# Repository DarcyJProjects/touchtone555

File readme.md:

# TouchTone555 – NE555 Analogue Stylus Synth

The **TouchTone555** is a fully analogue, NE555-based synthesizer designed for learning about analogue electronics, and a bit of fun too. It was built from scratch as a personal deep-dive into oscillators, signal integrity, analogue filtering, and amplification.

Read the full project write up at: [www.darcyjprojects.xyz](https://www.darcyjprojects.xyz/index.php/2025/04/07/analogue-synth-project-touchtone555/)

[🔗 Share this project on LinkedIn](https://www.linkedin.com/shareArticle?mini=true&url=https://www.darcyjprojects.xyz/index.php/2025/04/07/analogue-synth-project-touchtone555/&title=TouchTone555%20Stylus%20Synth&summary=Check%20out%20this%20analogue%20NE555-based%20synthesizer%20project!)

<p>
  This project is open source hardware under the <strong>CERN Open Hardware Licence Version 2 - Strongly Reciprocal (CERN-OHL-S v2)</strong>.
</p>

⚖️**Disclaimer:** This synthesizer was developed as a purely educational project to explore analogue electronics and sound synthesis. It is an independent work inspired by the vintage Stylophone, with no affiliation to Dubreq Ltd. or the original Stylophone product. All trademarks remain the property of their respective owners, and no copyright or trademark infringement is intended.

---

## 📑 Table of Contents

* 🎛 [Features](#-features)

* 📷 [Demo](#-demo)

* 📜 [Licence](#-licence)

* ⚡[How It Works](#how-it-works)

* 🛠️ [Build Instructions](#%EF%B8%8F-build-instructions)
  
  * 🧾 [What You’ll Need](#-what-youll-need)
  
  * 🪛 [Assembly](#-assembly)

* 📂 [Repo Structure](#-repo-structure)

* 💬 [Feedback & Contributions](#-feedback--contributions)

* 🔗 [Acknowledgements](#-acknowledgements)

* 🧠 [Why I Built This](#-why-i-built-this)

---

## 🎛 Features

- Based on the NE555 in astable multivibrator configuration as the main audio oscillator
- Individually tuneable keys with trim potentiometers
- Touch interface for the keys with a stylus
- Octave switching via capacitor bank selection
- Vibrato modulation using an RC oscillator on the 555's CV pin
- Push-pull amplifier output with an LM386 buffer stage
- Onboard speaker with volume control, as well as a headphone output
- Custom designed PCB, with a descriptive silkscreen

---

## 📷 Demo

Check out the demo video here:<br>
👉 [Watch the video](https://www.youtube.com/watch?v=lvPiY5EYj-0)<br>
<br>
🎵 Features a cover of Littleroot Town from Pokémon.

---

## 📜 Licence

This project is licenced under the **CERN-OHL-S v2 Strongly Reciprocal**.  

You are free to:

- **Study** and **modify** the design.

- **Make** and **sell** your own copies.

- **Distribute** modified versions — **as long as you:**
  
  - **Use the same CERN-OHL-S v2 licence** (strong reciprocity), and
  
  - **Provide attribution to the original author**, and
  
  - **Include the original source files and any modifications**.

For full details, see the [LICENCE.txt](https://github.com/DarcyJProjects/touchtone555/blob/main/LICENCE.txt) file.

---

## ⚡How It Works

The TouchTone555 generates sound using an NE555 timer IC which is configured as an astable multivibrator. 

Each key forms part of a series resistor network, which controls the oscillator’s frequency when the circuit is completed by touching a key with the stylus. The pitch is determined by which key is touched, and the selected octave capacitor.

Octave switching is achieved by toggling between banks of capacitors connected to the NE555. The more capacitance connected (capacitors in parallel), the lower the resulting octave.

Vibrato is achieved by modulating the NE555's control voltage pin using a separate RC oscillator, which uses RC (resistor-capacitor) pairs, capacitors, and a transistor to generate the low-frequency signal. The vibrato depth (or "mix") can be adjusted with the on-board trim potentiometer.

The output signal is then passed through an LM386 and then through a simple push-pull amplifier to drive the onboard speaker and/or headphones. The LM386 acts as a buffer to ensure any loading from the amplifier doesn't affect the NE555 through its output pin. The supply voltage to the NE555 is also filtered with a resistor and capacitor to reduce any periodic voltage drop introduced by the amplifier.

The power supply circuitry is simple: it supports a 9V DC input via either a JST connector, or a DC barrel jack. Two diodes prevent reverse polarity and ensure that the inputs cannot backfeed each other. 

This project demonstrates the core concepts of oscillation, modulation, and amplification - no microcontroller required!

👉 For a full breakdown and more detail explanations, you can read the write-up here: [www.darcyjprojects.xyz](https://www.darcyjprojects.xyz/index.php/2025/04/07/analogue-synth-project-touchtone555/)

---

## 🛠️ Build Instructions

### 🧾 What You’ll Need

- All components as outlined in the [BOM (Bill-of-Materials)](https://github.com/DarcyJProjects/touchtone555/blob/main/hardware/bom.md)
- To find the correct switches, speaker, audio jack, etc, see [Miscellaneous Parts](https://github.com/DarcyJProjects/touchtone555/blob/main/hardware/misc_parts.md)
- PCB (See [KiCad Project](https://github.com/DarcyJProjects/touchtone555/tree/main/hardware))
- Soldering iron and solder
- 9V Battery and connector or DC jack with 9V supply

⚠️ **Note:** I recommend selecting a **lead-free surface finish** (e.g., LeadFree HASL) when ordering the PCB as the stylus will put microscopic scratches in the exposed key pads during use. This could potentially produce harmful lead dust over time. Therefore, I highly recommend choosing lead-free!

### 🪛 Assembly

- Read each step fully before completing it to make sure you've read any handy tips :)
1. **Order the PCB**<br>
   The KiCad project files (and pre-exported gerber files) are located in [/hardware](https://github.com/DarcyJProjects/touchtone555/tree/main/hardware).

2. **Solder components in order**<br>
   Start with the smallest passive components (resistors, monolithic capacitors, diodes), then IC sockets, transistors, connectors/jacks/switches, ceramic and polyester capacitors, and finally the DC jack, trim potentiometers and the volume potentiometer.
   
   Soldering them systematically from smallest height to largest makes it a lot easier! Follow the component designators on the board, and in the BOM to make sure you are matching the correct values and components.
   
   Try your best not to get any solder on the exposed key pads, if you're nervous, you  can tape over them with some electrical or painters tape until you're finished soldering.
   
   For the polyester octave capacitors, try to get the values matched to each other as closely as possible as a small variance of 0.5 nF can throw off the pitch. This is less important for the lower octaves, but the highest octave with the single capacitor matters the most.
   
   For the vibrato monolithic capacitors, you can start with soldering the top three in, and adding the lower two if you want increase the vibrato frequency.

3. **Attach speaker & power**<br>
   The synth is designed to run on 9VDC, so I recommend using a 9V battery with a 9V battery to JST connector.

4. **Stylus**<br>
   
   In [/hardware](https://github.com/DarcyJProjects/touchtone555/tree/main/hardware), there is a 3D model of a stylus if you'd like to 3D print one, otherwise, a crocodile lead works really well too - just be careful not to push down too aggressively as to not damage the key pads.
   
   If you take the 3D model route, you can feed a thin gauge wire through the hole in the centre of the stylus, and solder a small piece of metal to the wire at the tip of the stylus. I used a mini spade connector which I soldered and then bent around the tip. I smoothed out the contact surface by creating a sphere of solder. You'll need to tape the tip to the stylus to ensure it doesn't come off. This stylus isn't perfect, but it works :)

5. **Tune keys**<br>
   Use a tuner app (with a chromatic mode) or oscilloscope to set the individual key pitches via the blue trim potentiometers.
   
   Set the octave to the lowest octave (lowest position on the octave switch) and then start tuning with the highest note on the keyboard, which corresponds to the right-most trim pot. Turning it clockwise will increase the pitch, and anticlockwise will decrease the pitch. You are aiming for the highest note (in the lowest octave) to be E6.
   
   Then work your way leftwards, one potentiometer at a time, reducing the pitch by one semitone each time.
   
   Remember, as this is a series resistor network, adjusting the pitch of one potentiometer will adjust the pitch of all the other keys to the left of that key. This is why you should work right to left.

6. **Vibrato depth**<br>
   By turning the vibrato depth trim pot, you can slightly adjust how strong the vibrato effect is. The change with each turn is minimal, so you'll need to turn it a lot to get any real difference. 

7. **Have fun!**

---

## 📂 Repo Structure

TouchTone555/<br>├── hardware/ # KiCad project + Gerbers + Stylus 3D model<br>├── media/ # Photos, demo videos, renders, etc<br>├── LICENCE # CERN-OHL-S v2<br>└── README.md # this file!<br>

---

### 💬 Feedback & Contributions

Feel free to fork, share, and build your own!<br>
If you build one, I’d love to see it - tag me on [LinkedIn](https://www.linkedin.com/in/darcywdjohnson/).

---

### 🔗 Acknowledgements

- This is an independent work inspired by the classic Stylophone with no affiliation to Dubreq Ltd. or the original Stylophone product. All trademarks remain the property of their respective owners, and no copyright or trademark infringement is intended.
- "Littleroot Town", composed by Gō Ichinose, Junichi Masuda, & Morikazu Aoki, from *Pokémon Ruby, Sapphire, & Emerald* (© Nintendo / Game Freak), is used under fair use as part of an educational demonstration.

---

## 🧠 Why I Built This

This was a personal challenge to push my understanding of analogue electronics beyond textbooks — especially in:

- Oscillator design
- Filtering
- Operational amplifiers
- Audio amplifiers
- Impedance buffering
- PCB design with custom exposed planes (the key pads)
- PCB footprint design

---

🛠️ Built for learning.<br>
❤️ Shared with the community.<br>
🔧 Darcy — [www.darcyjprojects.xyz](https://www.darcyjprojects.xyz)

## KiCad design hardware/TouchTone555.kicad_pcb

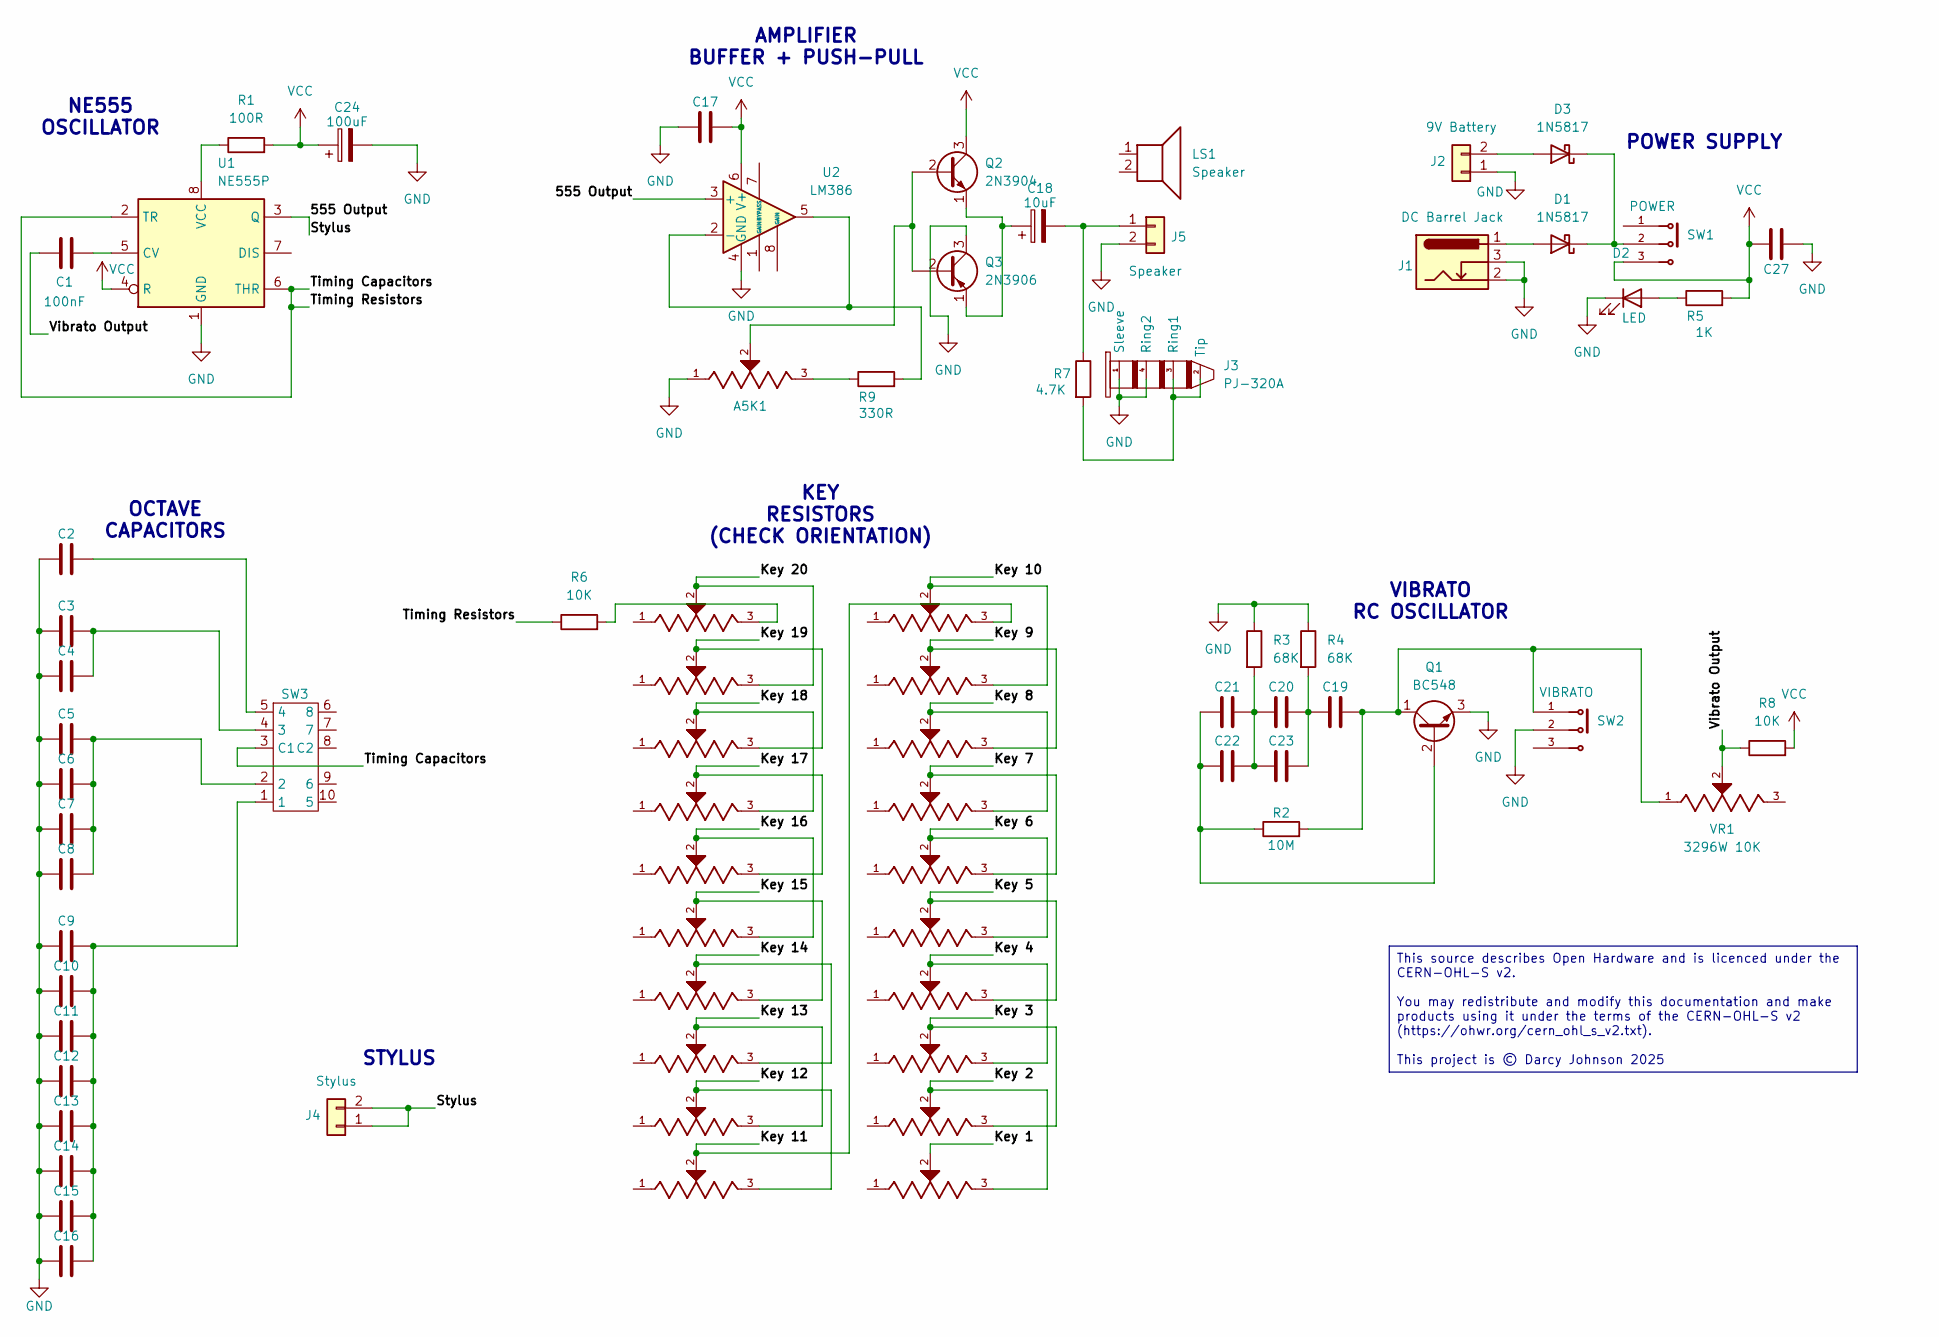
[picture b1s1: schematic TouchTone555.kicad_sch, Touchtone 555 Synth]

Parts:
A5K1: A5K RK097; RV09 Vertical Aliexpress; PARTREV 05/16
C1, C17, C19, C20, C21, C22, C23, C27: 100nF; C_Disc_D5.0mm_W2.5mm_P5.00mm
C2, C3, C4, C5, C6, C7, C8, C9, C10, C11, C12, C13, C14, C15, C16: 10nF; C_Rect_L7.0mm_W2.0mm_P5.00mm
C18: 10uF; CP_Radial_D5.0mm_P2.50mm
C24: 100uF; CP_Radial_D5.0mm_P2.50mm
D1, D3: 1N5817; D_DO-41_SOD81_P10.16mm_Horizontal
D2: LED; LED_D3.0mm
J1: DC Barrel Jack; BarrelJack_CUI_PJ-102AH_Horizontal_BIGGER_HOLES
J2: 9V Battery; JST_PH_B2B-PH-K_1x02_P2.00mm_Vertical
J3: PJ-320A
J4: Stylus; JST_PH_B2B-PH-K_1x02_P2.00mm_Vertical
J5: Speaker; JST_PH_B2B-PH-K_1x02_P2.00mm_Vertical
LS1: Speaker; 8Ω Speaker 40mm
Q1: BC548; TO-92_Inline
Q2: 2N3904; TO-92_Inline
Q3: 2N3906; TO-92_Inline
R1: 100R; R_Axial_DIN0207_L6.3mm_D2.5mm_P7.62mm_Horizontal
R2: 10M; R_Axial_DIN0207_L6.3mm_D2.5mm_P7.62mm_Horizontal
R3, R4: 68K; R_Axial_DIN0207_L6.3mm_D2.5mm_P7.62mm_Horizontal
R5: 1K; R_Axial_DIN0207_L6.3mm_D2.5mm_P7.62mm_Horizontal
R6, R8: 10K; R_Axial_DIN0207_L6.3mm_D2.5mm_P7.62mm_Horizontal
R7: 4.7K; R_Axial_DIN0207_L6.3mm_D2.5mm_P7.62mm_Horizontal
R9: 330R; R_Axial_DIN0207_L6.3mm_D2.5mm_P7.62mm_Horizontal
SW1: POWER; SW_1825159-1; MPN 1825159-1
SW2: VIBRATO; SW_1825159-1; MPN 1825159-1
SW3: SS-24E04_2P4T_Slide_Switch
U1: NE555P; DIP-8_W7.62mm
U2: LM386; DIP-8_W7.62mm
VR1: 3296W 10K; Potentiometer_Bourns_3296W_Vertical; PARTREV 05/16
VR2, VR3, VR4, VR5, VR6, VR7, VR8, VR9, VR10, VR11, VR13, VR14, VR15, VR16, VR17, VR18, VR19, VR20, VR21, VR22: 3296W 5K; Potentiometer_Bourns_3296W_Vertical; PARTREV 05/16

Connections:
/555 Output: J4.1, J4.2, U1.3 (Q), U2.3 (+)
/Key 1: VR22.2
/Key 2: VR21.2, VR22.3
/Key 3: VR20.2, VR21.3
/Key 4: VR19.2, VR20.3
/Key 5: VR18.2, VR19.3
/Key 6: VR17.2, VR18.3
/Key 7: VR16.2, VR17.3
/Key 8: VR15.2, VR16.3
/Key 9: VR14.2, VR15.3
/Key 10: VR13.2, VR14.3
/Key 11: VR11.2, VR13.3
/Key 12: VR10.2, VR11.3
/Key 13: VR9.2, VR10.3
/Key 14: VR8.2, VR9.3
/Key 15: VR7.2, VR8.3
/Key 16: VR6.2, VR7.3
/Key 17: VR5.2, VR6.3
/Key 18: VR4.2, VR5.3
/Key 19: VR3.2, VR4.3
/Key 20: VR2.2, VR3.3
/Timing Capacitors: R6.1, SW3.3 (C1), U1.2 (TR), U1.6 (THR)
/Vibrato Output: C1.2, R8.1, VR1.2
GND: A5K1.1, C2.1, C3.1, C4.1, C5.1, C6.1, C7.1, C8.1, C9.1, C10.1, C11.1, C12.1, C13.1, C14.1, C15.1, C16.1, C17.1, C24.2, C27.1, D2.1 (K), J1.2, J1.3, J2.1, J3.1 (Sleeve), J3.4 (Ring2), J5.2, Q1.3 (E), Q3.3 (C), R3.1, R4.1, SW2.2, U1.1 (GND), U2.4 (GND)
unnamed: A5K1.3, R9.1
unnamed: C5.2, C6.2, C7.2, C8.2, SW3.2
unnamed: C9.2, C10.2, C11.2, C12.2, C13.2, C14.2, C15.2, C16.2, SW3.1
unnamed: C19.1, C20.2, C23.2, R4.2
unnamed: C20.1, C21.2, C22.2, C23.1, R3.2
unnamed: D1.2 (A), J1.1
unnamed: D1.1 (K), D3.1 (K), SW1.2
unnamed: D2.2 (A), R5.1
unnamed: D3.2 (A), J2.2
unnamed: J3.2 (Tip), J3.3 (Ring1), R7.2
unnamed: C18.2, J5.1, R7.1
unnamed: C21.1, C22.1, Q1.2 (B), R2.1
unnamed: C19.2, Q1.1 (C), R2.2, SW2.1, VR1.1
unnamed: A5K1.2, Q2.2 (B), Q3.2 (B)
unnamed: C18.1, Q2.1 (E), Q3.1 (E)
unnamed: R6.2, VR2.3
unnamed: C3.2, C4.2, SW3.4 (3)
unnamed: C2.2, SW3.5 (4)
unnamed: C1.1, U1.5 (CV)
unnamed: R1.1, U1.8 (VCC)
unnamed: R9.2, U2.2 (-), U2.5
VCC: C17.2, C24.1, C27.2, Q2.3 (C), R1.2, R5.2, R8.2, SW1.3, U1.4 (R), U2.6 (V+)

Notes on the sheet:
NE555 OSCILLATOR
STYLUS
VIBRATO RC OSCILLATOR
KEY RESISTORS (CHECK ORIENTATION)
OCTAVE CAPACITORS
AMPLIFIER BUFFER + PUSH-PULL
POWER SUPPLY
This source describes Open Hardware and is licenced under the CERN-OHL-S v2. You may redistribute and modify this documentation and make products using it under the terms of the CERN-OHL-S v2 (https://ohwr.org/cern_ohl_s_v2.txt). This project is © Darcy Johnson 2025

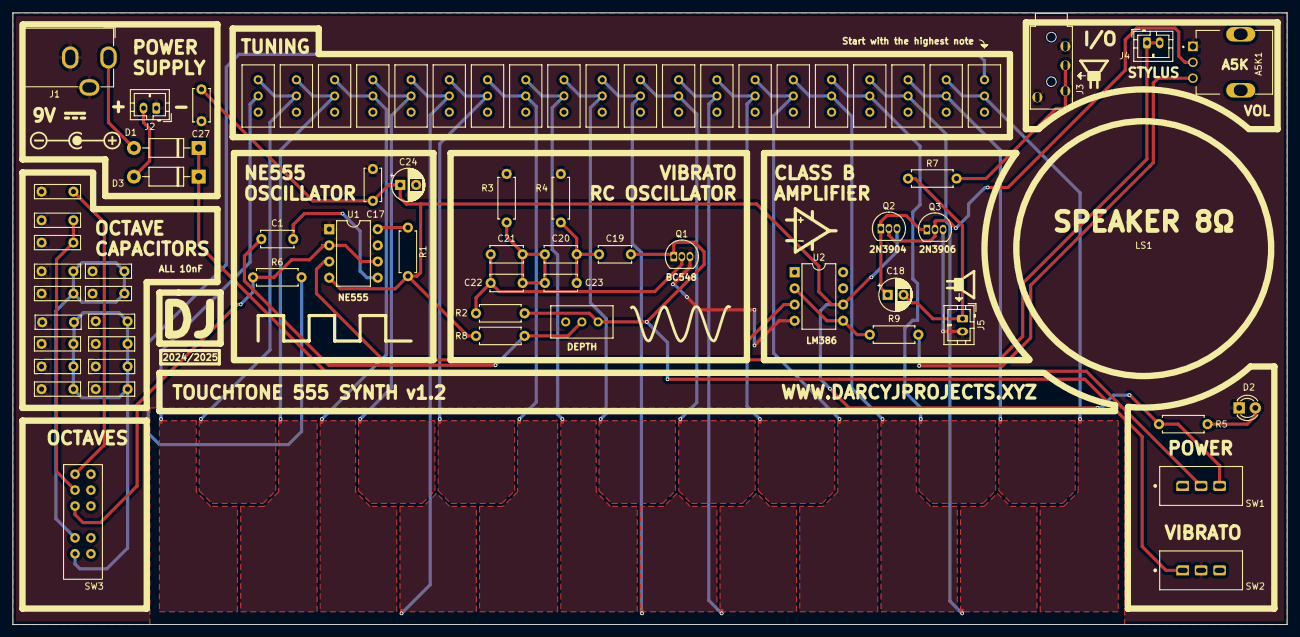
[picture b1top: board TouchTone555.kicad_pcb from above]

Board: 2 copper layers, 200.0 x 96.0 mm, 73 parts (0 on the bottom side), 45 nets.

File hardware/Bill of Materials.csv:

"Id;""Designator"";""Footprint"";""Quantity"";""Designation"";""Supplier and ref"";",,,,,,,,,,,,,,,,,,,
"1;""D1","D3"";""D_DO-41_SOD81_P10.16mm_Horizontal"";2;""1N5817"";;;",,,,,,,,,,,,,,,,,,
"2;""SW3"";""SS-24E04_2P4T_Slide_Switch"";1;""~"";;;",,,,,,,,,,,,,,,,,,,
"3;""R7"";""R_Axial_DIN0207_L6.3mm_D2.5mm_P7.62mm_Horizontal"";1;""4.7K"";;;",,,,,,,,,,,,,,,,,,,
"4;""R1"";""R_Axial_DIN0207_L6.3mm_D2.5mm_P7.62mm_Horizontal"";1;""100R"";;;",,,,,,,,,,,,,,,,,,,
"5;""C18"";""CP_Radial_D5.0mm_P2.50mm"";1;""10uF"";;;",,,,,,,,,,,,,,,,,,,
"6;""SW2"";""SW_1825159-1"";1;""VIBRATO"";;;",,,,,,,,,,,,,,,,,,,
"7;""J4"";""JST_PH_B2B-PH-K_1x02_P2.00mm_Vertical"";1;""Stylus"";;;",,,,,,,,,,,,,,,,,,,
"8;""VR15",VR4,VR5,VR8,VR22,VR11,VR20,VR14,VR9,VR17,VR3,VR6,VR10,VR2,VR13,VR18,VR19,VR7,VR21,"VR16"";""Potentiometer_Bourns_3296W_Vertical"";20;""3296W 5K"";;;"
"9;""C6",C16,C7,C11,C5,C9,C15,C2,C13,C3,C12,C14,C8,C4,"C10"";""C_Rect_L7.0mm_W2.0mm_P5.00mm"";15;""10nF"";;;",,,,,
"10;""Q3"";""TO-92_Inline"";1;""2N3906"";;;",,,,,,,,,,,,,,,,,,,
"11;""C21",C19,C27,C17,C20,C1,C23,"C22"";""C_Disc_D5.0mm_W2.5mm_P5.00mm"";8;""100nF"";;;",,,,,,,,,,,,
"12;""R2"";""R_Axial_DIN0207_L6.3mm_D2.5mm_P7.62mm_Horizontal"";1;""10M"";;;",,,,,,,,,,,,,,,,,,,
"13;""R6","R8"";""R_Axial_DIN0207_L6.3mm_D2.5mm_P7.62mm_Horizontal"";2;""10K"";;;",,,,,,,,,,,,,,,,,,
"14;""R5"";""R_Axial_DIN0207_L6.3mm_D2.5mm_P7.62mm_Horizontal"";1;""1K"";;;",,,,,,,,,,,,,,,,,,,
"15;""R9"";""R_Axial_DIN0207_L6.3mm_D2.5mm_P7.62mm_Horizontal"";1;""330R"";;;",,,,,,,,,,,,,,,,,,,
"16;""U2"";""DIP-8_W7.62mm"";1;""LM386"";;;",,,,,,,,,,,,,,,,,,,
"17;""Q1"";""TO-92_Inline"";1;""BC548"";;;",,,,,,,,,,,,,,,,,,,
"18;""J1"";""BarrelJack_CUI_PJ-102AH_Horizontal_BIGGER_HOLES"";1;""DC Barrel Jack"";;;",,,,,,,,,,,,,,,,,,,
"19;""Q2"";""TO-92_Inline"";1;""2N3904"";;;",,,,,,,,,,,,,,,,,,,
"20;""R4","R3"";""R_Axial_DIN0207_L6.3mm_D2.5mm_P7.62mm_Horizontal"";2;""68K"";;;",,,,,,,,,,,,,,,,,,
"21;""U1"";""DIP-8_W7.62mm"";1;""NE555P"";;;",,,,,,,,,,,,,,,,,,,
"22;""J5"";""JST_PH_B2B-PH-K_1x02_P2.00mm_Vertical"";1;""Speaker"";;;",,,,,,,,,,,,,,,,,,,
"23;""C24"";""CP_Radial_D5.0mm_P2.50mm"";1;""100uF"";;;",,,,,,,,,,,,,,,,,,,
"24;""J2"";""JST_PH_B2B-PH-K_1x02_P2.00mm_Vertical"";1;""9V Battery"";;;",,,,,,,,,,,,,,,,,,,
"25;""A5K1"";""RV09 Vertical Aliexpress"";1;""A5K RK097"";;;",,,,,,,,,,,,,,,,,,,
"26;""LS1"";""8Ω Speaker 40mm"";1;""Speaker"";;;",,,,,,,,,,,,,,,,,,,
"27;""VR1"";""Potentiometer_Bourns_3296W_Vertical"";1;""3296W 10K"";;;",,,,,,,,,,,,,,,,,,,
"28;""SW1"";""SW_1825159-1"";1;""POWER"";;;",,,,,,,,,,,,,,,,,,,
"29;""J3"";""PJ-320A"";1;""PJ-320A"";;;",,,,,,,,,,,,,,,,,,,
"30;""D2"";""LED_D3.0mm"";1;""LED"";;;",,,,,,,,,,,,,,,,,,,

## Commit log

2025-05-17 Added initial photos
2025-05-17 Media Upload
2025-05-17 Upload KiCad project, fabrication files
2025-05-17 Add readme
2025-05-17 Update readme.md
    Added <br> to force new lines
2025-05-17 Upload misc_part images
2025-05-18 Stylus model, how it works
2025-05-18 Image file size reduction
2025-05-25 Add board render, schematic
2025-06-26 Fixed values for trim pots & R8
    Tuning trim potentiometers were incorrectly listed as 10K, have been changed to 5K.
    Vibrato trim potentiometer was incorrectly listed as 250R, has been changed to 10K.
    R8 was incorrectly listed as 20K, should be 10K.
2025-10-24 Added a bom.md file
    Easier to read than csv.
2025-10-24 Update readme.md
    Updated BOM link to md rather than csv
2025-10-24 Update bom.md
    Added links to misc_parts.md
